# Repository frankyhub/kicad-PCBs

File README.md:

# KiCad-PCBs

Printed Circuit Boards - Vorlagen
- Download kicad: https://kicad-pcb.org/download/
- Docs kicad: https://docs.kicad-pcb.org/

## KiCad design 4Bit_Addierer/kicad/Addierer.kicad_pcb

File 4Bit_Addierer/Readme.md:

## 4-Bit Addierer Frontplatte und Platine

### Frontplatte

### Platine

### Schaltplan

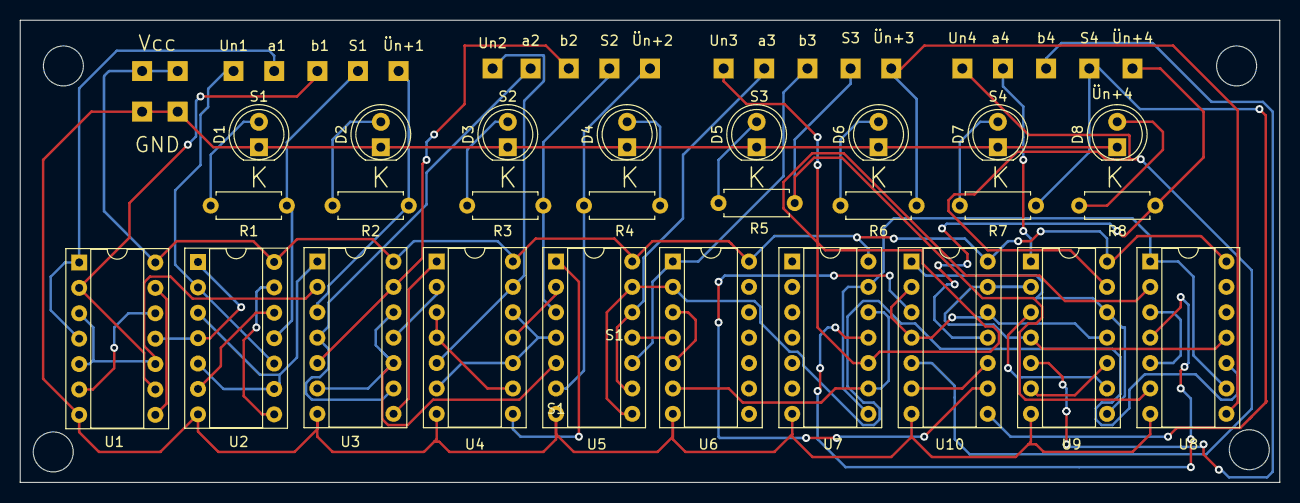
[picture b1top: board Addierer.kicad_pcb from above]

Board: 2 copper layers, 126.0 x 46.2 mm, 50 parts (0 on the bottom side), 58 nets.

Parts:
D1, D2, D3, D4, D5, D6, D7, D8: LED; LED_D5.0mm
GND1, GND1#3: LP_GND; LP
GND1#2: GND; LP
LP_Vcc1: LP_Vcc; LP
R1, R2, R3, R4, R5, R6, R7, R8: R; R_Axial_DIN0207_L6.3mm_D2.5mm_P7.62mm_Horizontal
S1: S1; LP
S2: S2; LP
S3: S3; LP
S4: S4; LP
U1, U2, U3, U4, U5, U6, U7, U8, U9, U10: 74LS00; DIP-14_W7.62mm_Socket
Un1: Un1; LP
Un2: Un2; LP
Un3: Un3; LP
Un4: Un4; LP
a1: a1; LP
a2: a2; LP
a3: a3; LP
a4: a4; LP
b1: b1; LP
b2: b2; LP
b3: b3; LP
b4: b4; LP
Ün+1: Ün+1; LP
Ün+2: Ün+2; LP
Ün+3: Ün+3; LP
Ün+4: Ün+4; LP

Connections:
+5V: GND1#2.1, LP_Vcc1.1, U1.14, U2.14, U3.14, U4.14, U5.14, U6.14, U7.14, U8.14, U9.14, U10.14
unnamed: D1.2, R1.2
unnamed: D2.2, R2.2
unnamed: D3.2, R3.2
unnamed: D4.2, R4.2
unnamed: D5.2, R5.2
unnamed: D6.2, R6.2
unnamed: D7.2, R7.2
unnamed: D8.2, R8.2
unnamed: D1.1, D2.1, D3.1, D4.1, D5.1, D6.1, D7.1, D8.1, GND1.1, GND1#3.1, U1.7, U2.7, U3.7, U4.7, U5.7, U6.7, U7.7, U8.7, U9.7, U10.7
unnamed: R1.1, S1.1, U2.11
unnamed: R2.1, U3.3, Ün+1.1
unnamed: R3.1, S2.1, U5.3
unnamed: R4.1, U5.6, Ün+2.1
unnamed: R5.1, S3.1, U8.6
unnamed: R6.1, U8.8, Ün+3.1
unnamed: R7.1, S4.1, U10.8
unnamed: R8.1, U10.11, Ün+4.1
unnamed: U1.1, U1.4, a1.1
unnamed: U1.2, U1.9, b1.1
unnamed: U1.3, U1.5, U1.10, U3.2
unnamed: U1.11, U2.1, U2.4
unnamed: U1.6, U1.12
unnamed: U1.8, U1.13
unnamed: U2.3, U2.5, U2.9, U3.1
unnamed: U2.2, U2.10, Un1.1
unnamed: U2.6, U2.12
unnamed: U2.8, U2.13
unnamed: U3.4, U3.9, a2.1
unnamed: U3.8, U4.1
unnamed: U3.6, U3.10, U3.12, U5.5
unnamed: U3.11, U4.2
unnamed: U3.5, U3.13, b2.1
unnamed: U4.3, U4.4, U4.9
unnamed: U4.8, U5.1
unnamed: U4.6, U4.10, U4.12, U5.4
unnamed: U4.11, U5.2
unnamed: U4.5, U4.13, Un2.1
unnamed: U5.10, U6.1, b3.1
unnamed: U5.11, U6.4
unnamed: U5.9, U5.12, a3.1
unnamed: U5.8, U5.13, U6.2, U8.10
unnamed: U6.3, U6.5
unnamed: U6.6, U7.9, U7.12
unnamed: U7.10, U8.2, Un3.1
unnamed: U7.11, U8.4
unnamed: U7.8, U7.13, U8.1, U8.9
unnamed: U8.3, U8.5
unnamed: U9.1, a4.1
unnamed: U9.3, U9.9
unnamed: U9.5, b4.1
unnamed: U9.6, U9.10
unnamed: U9.8, U9.12, U10.1
unnamed: U10.3, U10.9
unnamed: U9.13, U10.5, Un4.1
unnamed: U10.6, U10.10
unnamed: U9.11, U10.2, U10.4, U10.12
unnamed: U8.11, U9.2, U9.4, U10.13

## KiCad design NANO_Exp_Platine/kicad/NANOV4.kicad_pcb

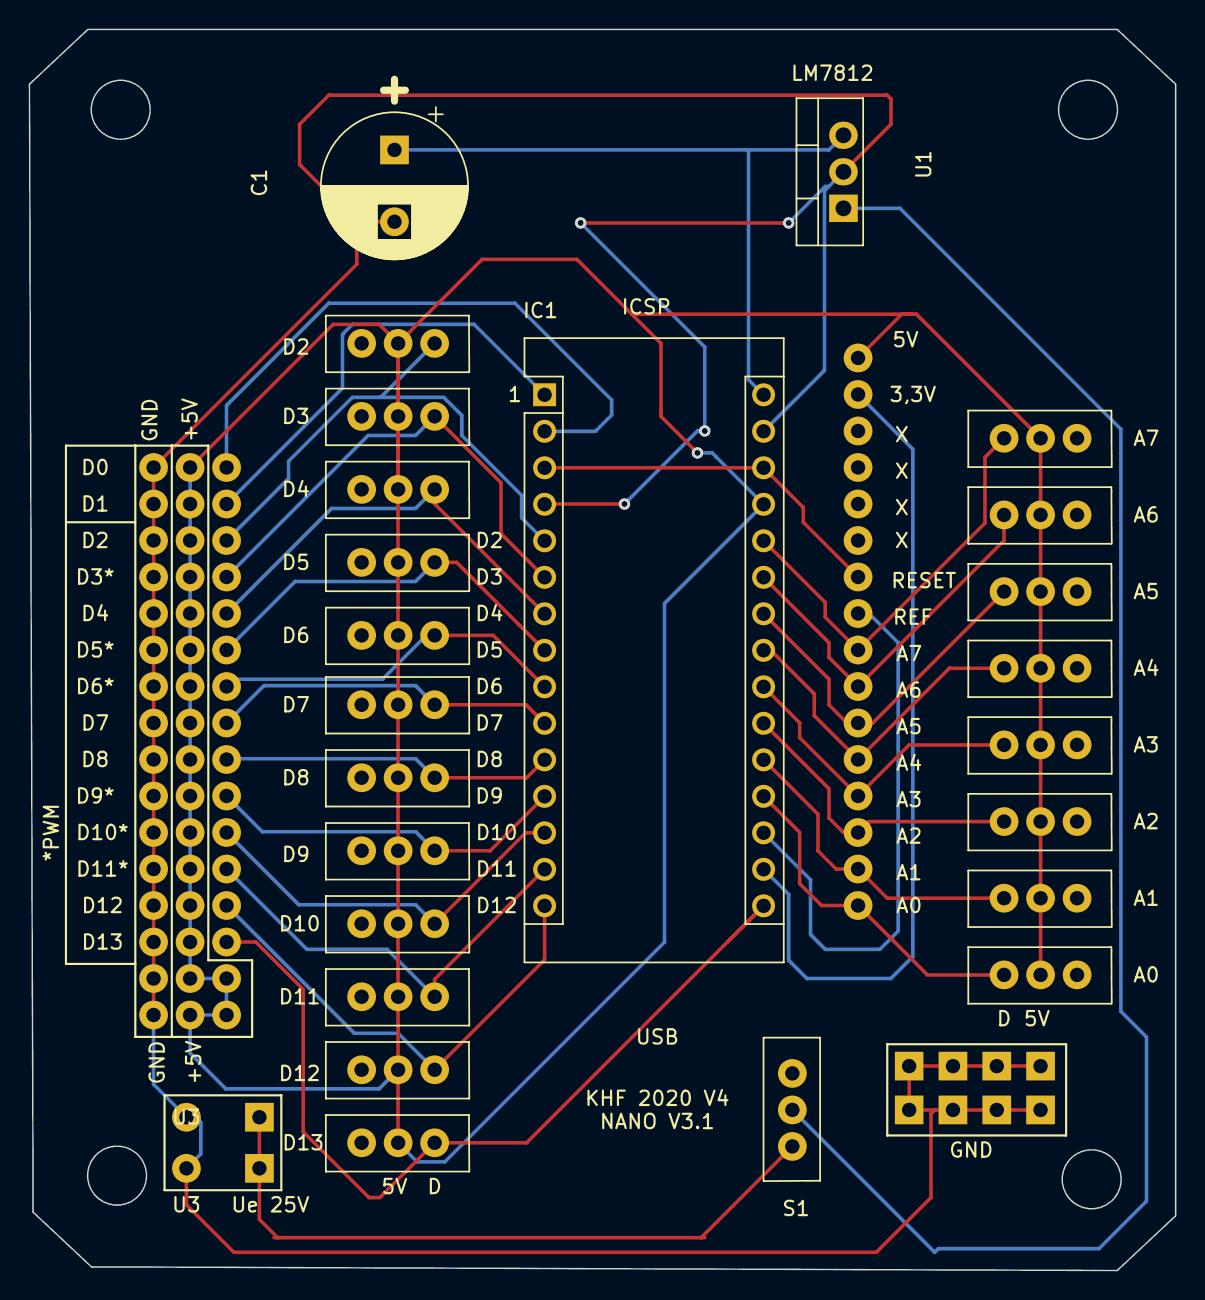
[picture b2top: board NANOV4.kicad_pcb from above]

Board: 2 copper layers, 79.8 x 86.4 mm, 38 parts (0 on the bottom side), 30 nets.

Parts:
A0, A1, A2, A3, A4, A5, A6, A7: Micro_Schalter; Micro_SchalterKHF
C1: CAP; CP_Radial_D10.0mm_P5.00mm
D2, D3, D4, D5, D6, D7, D8, D9, D10, D11, D12, D13: Micro_Schalter; Micro_SchalterKHF
IC1: Arduino_Nano_v3.x; Arduino_Nano
J1, J2, J3, J4: NANO16PINStiftleiste; NANO_Stift_16PIN
LP: LP
LP#2, LP#3, LP#4, LP#6, LP#7, LP#8: LP
LP#5: GND; LP
S1: Micro_Schalter; Micro_SchalterKHF
U1: LM7812_TO220; TO-220-3_Vertical
U3, U3#2: 9VBat; 9VBAT_khf

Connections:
+5V: A0.2, A1.2, A2.2, A3.2, A4.2, A5.2, A6.2, A7.2, D2.2, D3.2, D4.2, D5.2, D6.2, D7.2, D8.2, D9.2, D10.2, D11.2, D12.2, D13.2, IC1.27, J2.1, J2.2, J2.3, J2.4, J2.5, J2.6, J2.7, J2.8, J2.9, J2.10, J2.11, J2.12, J2.13, J2.14, J2.15, J2.16, J3.15, J3.16, J4.16
GND: C1.2, IC1.4, IC1.29, J1.1, J1.2, J1.3, J1.4, J1.5, J1.6, J1.7, J1.8, J1.9, J1.10, J1.11, J1.12, J1.13, J1.14, J1.15, J1.16, LP.1, LP#2.1, LP#3.1, LP#4.1, LP#5.1, LP#6.1, LP#7.1, LP#8.1, U1.2, U3.1, U3#2.1
unnamed: A0.3, IC1.19, J4.1
unnamed: A1.3, IC1.20, J4.2
unnamed: A2.3, IC1.21, J4.3
unnamed: A3.3, IC1.22, J4.4
unnamed: A4.3, IC1.23, J4.5
unnamed: A5.3, IC1.24, J4.6
unnamed: A6.3, IC1.25, J4.7
unnamed: A7.3, IC1.26, J4.8
unnamed: C1.1, IC1.30, U1.3
unnamed: D2.1, IC1.5, J3.3
unnamed: D3.1, IC1.6, J3.4
unnamed: D4.1, IC1.7, J3.5
unnamed: D5.1, IC1.8, J3.6
unnamed: D6.1, IC1.9, J3.7
unnamed: D7.1, IC1.10, J3.8
unnamed: D8.1, IC1.11, J3.9
unnamed: D9.1, IC1.12, J3.10
unnamed: D10.1, IC1.13, J3.11
unnamed: D11.1, IC1.14, J3.12
unnamed: D12.1, IC1.15, J3.13
unnamed: D13.1, IC1.16, J3.14
unnamed: IC1.1, J3.2
unnamed: IC1.2, J3.1
unnamed: IC1.17, J4.15
unnamed: IC1.18, J4.9
unnamed: IC1.3, IC1.28, J4.10
unnamed: S1.1, U3.2, U3#2.2
unnamed: S1.2, U1.1

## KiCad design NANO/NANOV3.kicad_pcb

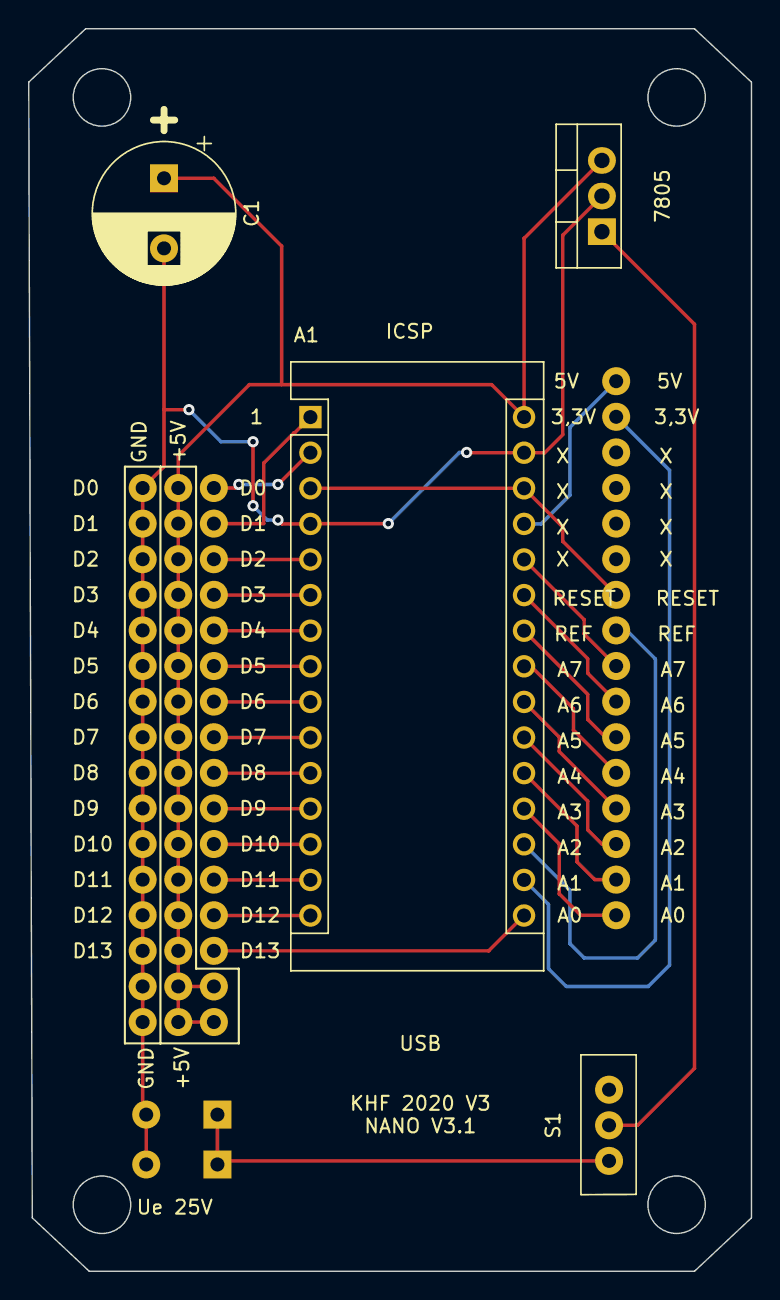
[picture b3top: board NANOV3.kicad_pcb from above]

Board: 2 copper layers, 51.6 x 88.6 mm, 10 parts (0 on the bottom side), 30 nets.

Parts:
7805: LM7805_TO220; TO-220-3_Vertical
A1: Arduino_Nano_v3.x; Arduino_Nano
C1: CAP; CP_Radial_D10.0mm_P5.00mm
J1, J2, J3, J4: NANO16PINStiftleiste; NANO_Stift_16PIN
S1: Micro_Schalter; Micro_SchalterKHF
U3, U3#2: 9VBat; 9VBAT_khf

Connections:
unnamed: A1.1, J3.2
unnamed: A1.2, J3.1
unnamed: A1.5, J3.3
unnamed: A1.6, J3.4
unnamed: A1.7, J3.5
unnamed: A1.8, J3.6
unnamed: A1.9, J3.7
unnamed: A1.10, J3.8
unnamed: A1.11, J3.9
unnamed: A1.12, J3.10
unnamed: A1.13, J3.11
unnamed: A1.14, J3.12
unnamed: A1.15, J3.13
unnamed: A1.16, J3.14
unnamed: A1.17, J4.15
unnamed: A1.18, J4.9
unnamed: A1.19, J4.1
unnamed: A1.20, J4.2
unnamed: A1.21, J4.3
unnamed: A1.22, J4.4
unnamed: A1.23, J4.5
unnamed: A1.24, J4.6
unnamed: A1.25, J4.7
unnamed: A1.26, J4.8
unnamed: A1.27, J4.16
unnamed: A1.3, A1.28, J4.10
unnamed: 7805.2, A1.4, A1.29, C1.2, J1.1, J1.2, J1.3, J1.4, J1.5, J1.6, J1.7, J1.8, J1.9, J1.10, J1.11, J1.12, J1.13, J1.14, J1.15, J1.16, U3.1, U3#2.1
unnamed: 7805.3, A1.30, C1.1, J2.1, J2.2, J2.3, J2.4, J2.5, J2.6, J2.7, J2.8, J2.9, J2.10, J2.11, J2.12, J2.13, J2.14, J2.15, J2.16, J3.15, J3.16
unnamed: S1.1, U3.2, U3#2.2
unnamed: 7805.1, S1.2

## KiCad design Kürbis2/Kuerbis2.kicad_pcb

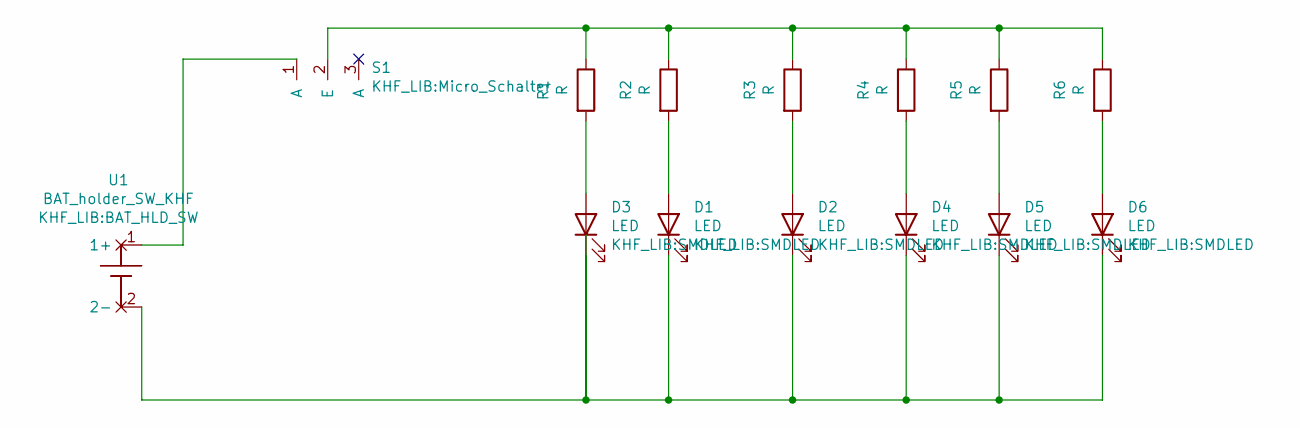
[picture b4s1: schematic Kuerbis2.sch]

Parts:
D1, D2, D3, D4, D5, D6: LED; SMDLED
R1, R2, R3, R4, R5, R6: R; R_Axial_DIN0309_L9.0mm_D3.2mm_P12.70mm_Horizontal
S1: Micro_Schalter
U1: BAT_holder_SW_KHF; BAT_HLD_SW

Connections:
unnamed: D1.1 (K), D2.1 (K), D3.1 (K), D4.1 (K), D5.1 (K), D6.1 (K), U1.2 (2-)
unnamed: D1.2 (A), R2.2
unnamed: D2.2 (A), R3.2
unnamed: D3.2 (A), R1.2
unnamed: D4.2 (A), R4.2
unnamed: D5.2 (A), R5.2
unnamed: D6.2 (A), R6.2
unnamed: R1.1, R2.1, R3.1, R4.1, R5.1, R6.1, S1.2 (E)
unnamed: S1.1 (A), U1.1 (1+)

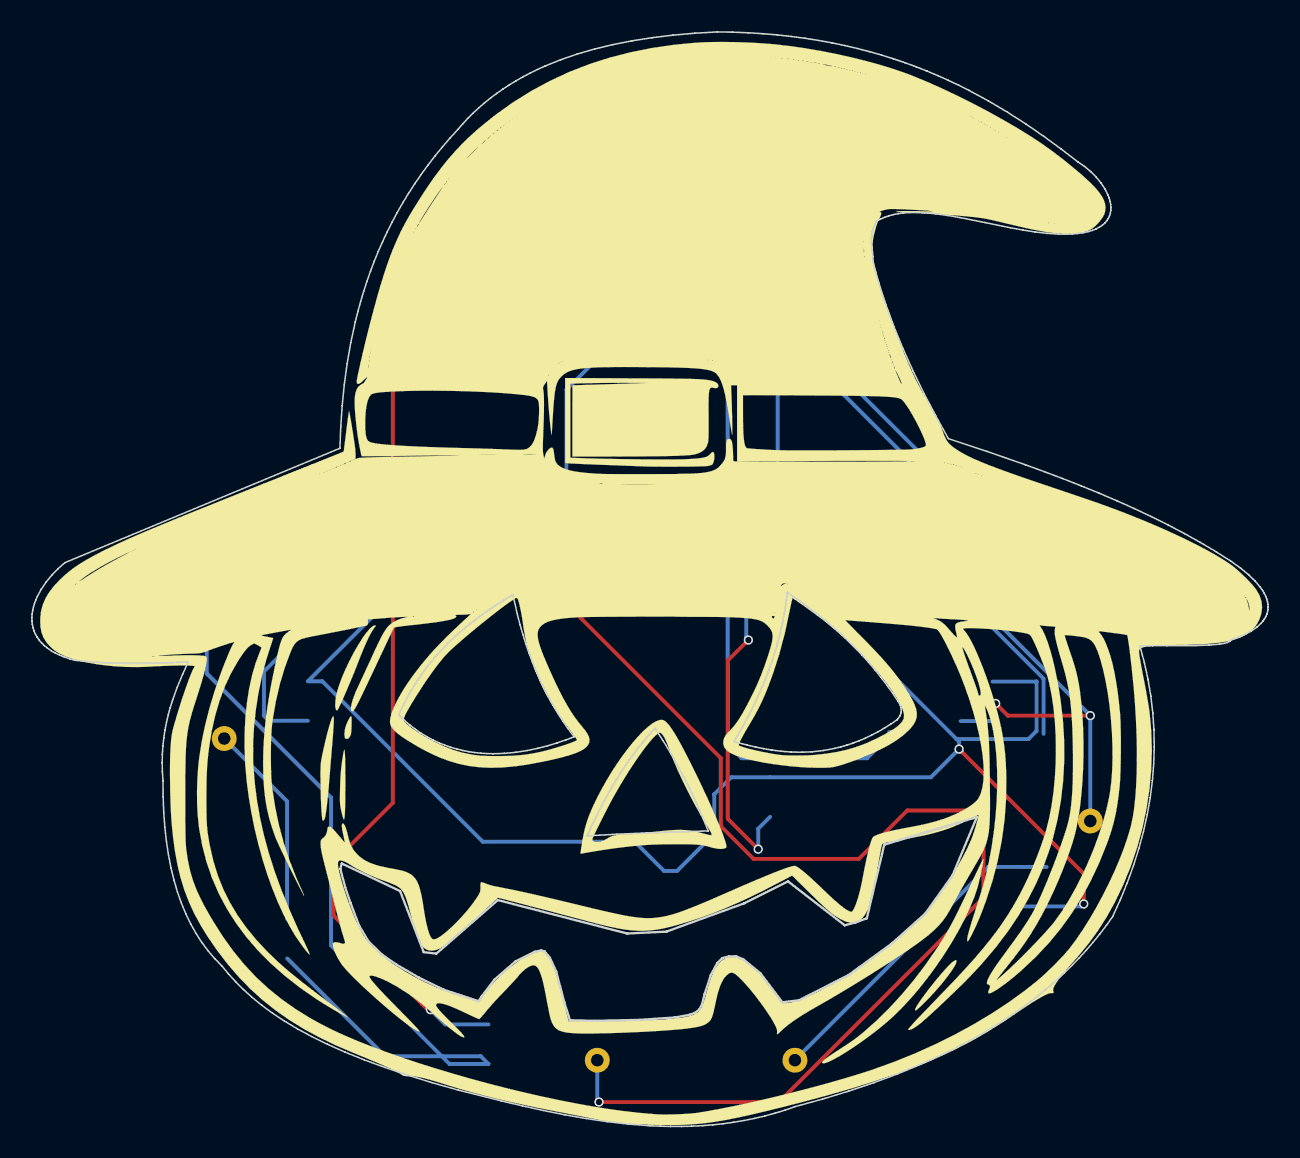
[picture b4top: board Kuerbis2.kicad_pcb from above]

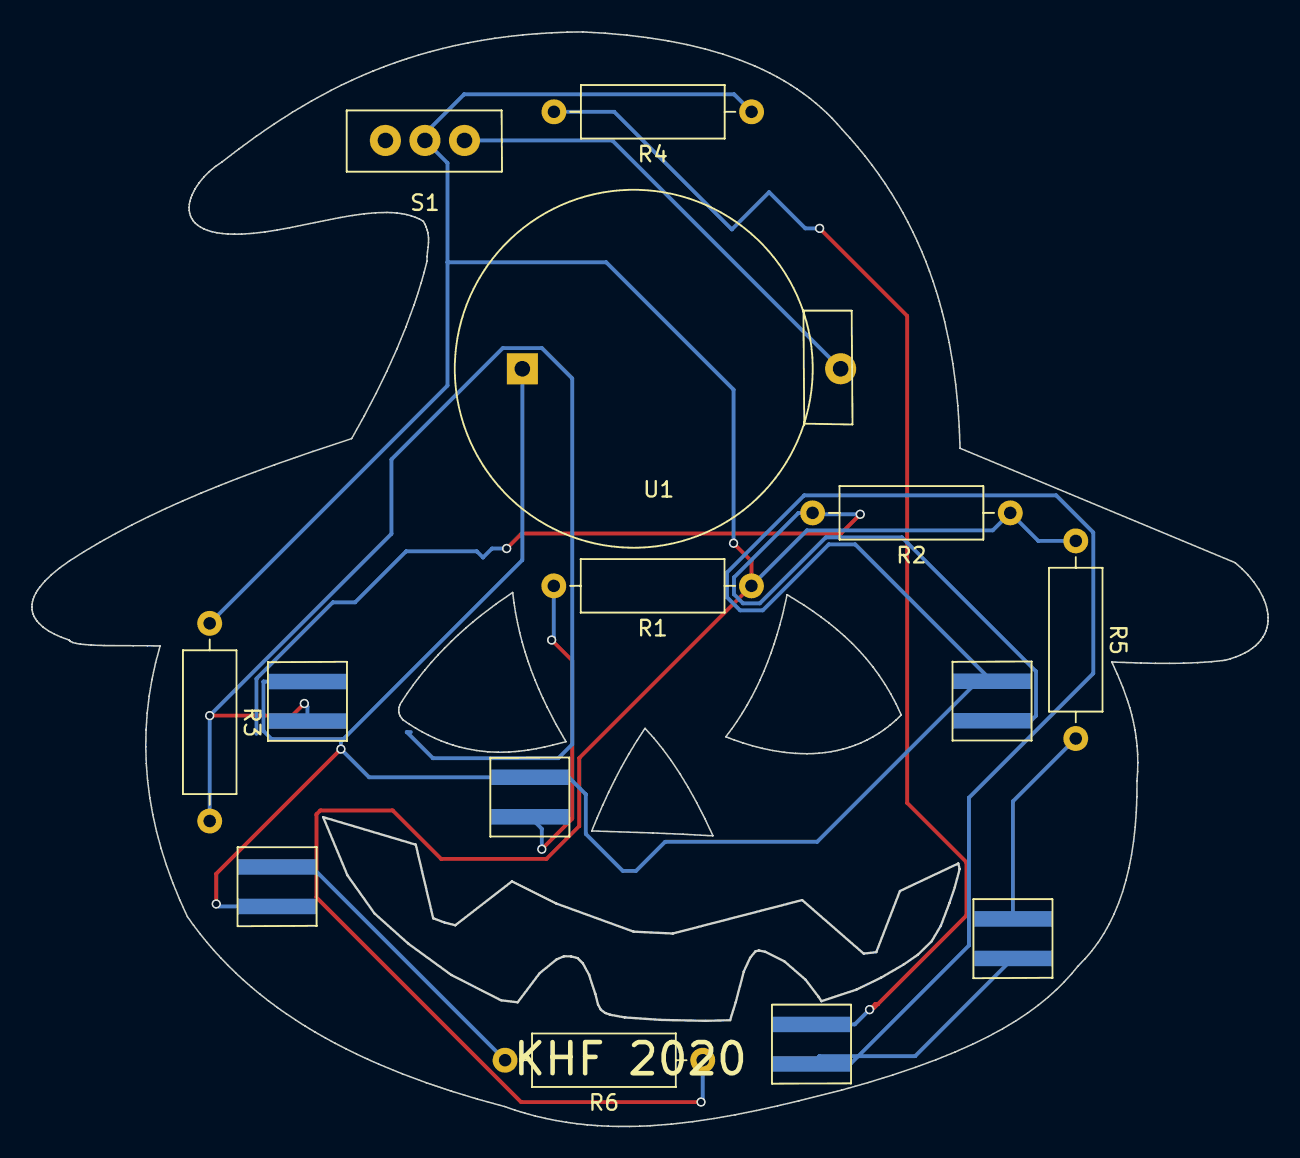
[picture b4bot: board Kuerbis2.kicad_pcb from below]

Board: 2 copper layers, 79.4 x 70.3 mm, 14 parts (14 on the bottom side), 9 nets.

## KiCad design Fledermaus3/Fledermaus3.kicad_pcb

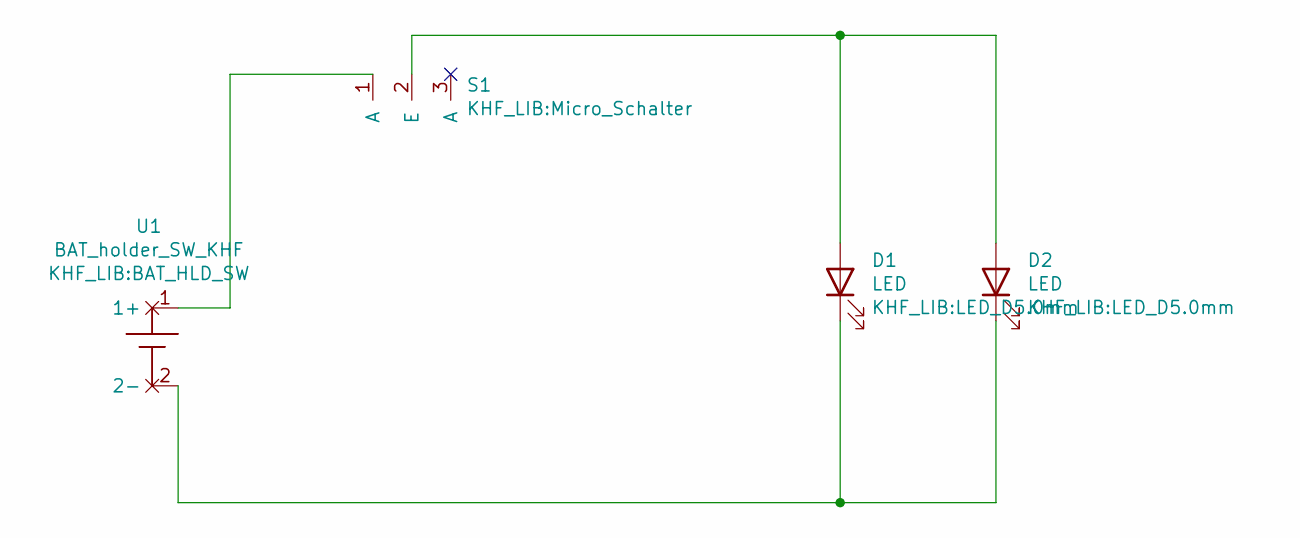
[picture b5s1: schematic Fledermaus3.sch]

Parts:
D1, D2: LED; LED_D5.0mm
S1: Micro_Schalter
U1: BAT_holder_SW_KHF; BAT_HLD_SW

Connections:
unnamed: D1.1 (K), D2.1 (K), U1.2 (2-)
unnamed: D1.2 (A), D2.2 (A), S1.2 (E)
unnamed: S1.1 (A), U1.1 (1+)

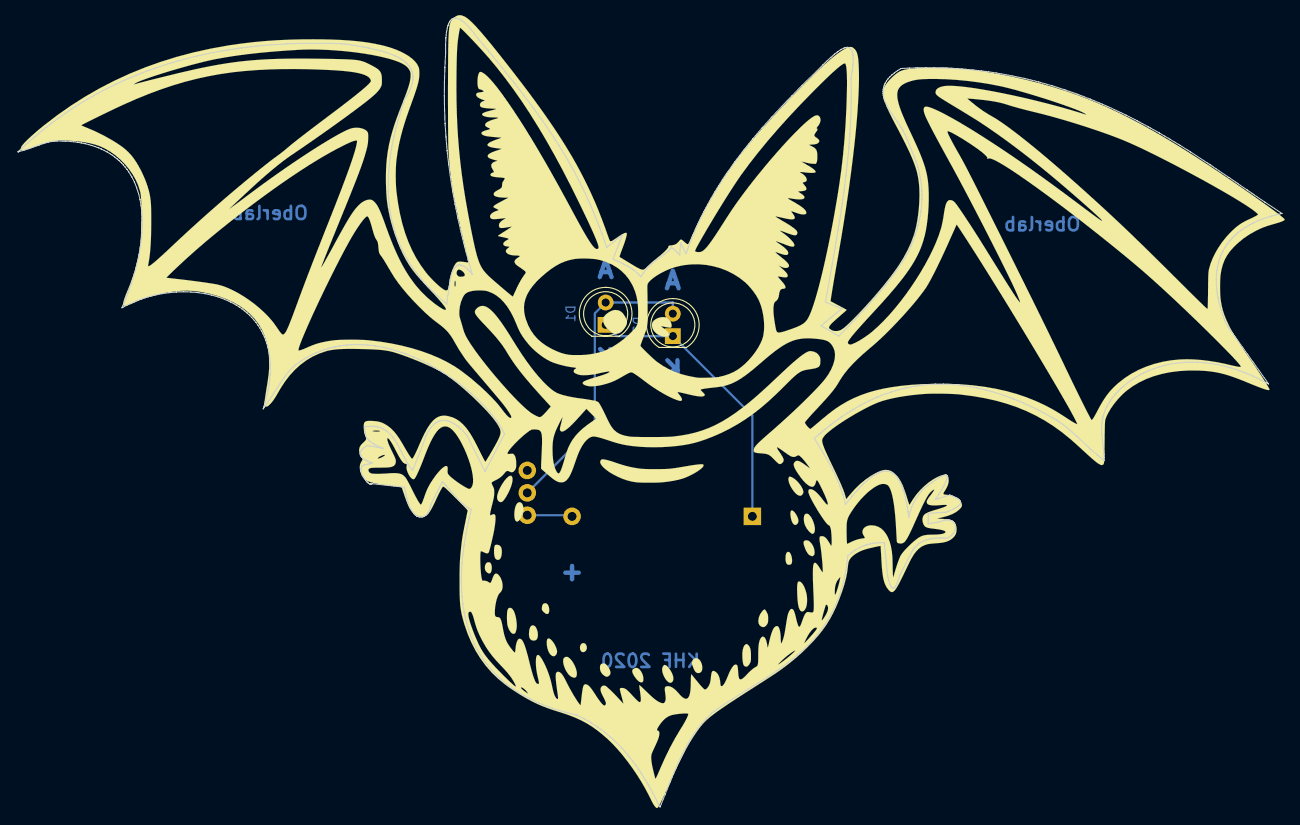
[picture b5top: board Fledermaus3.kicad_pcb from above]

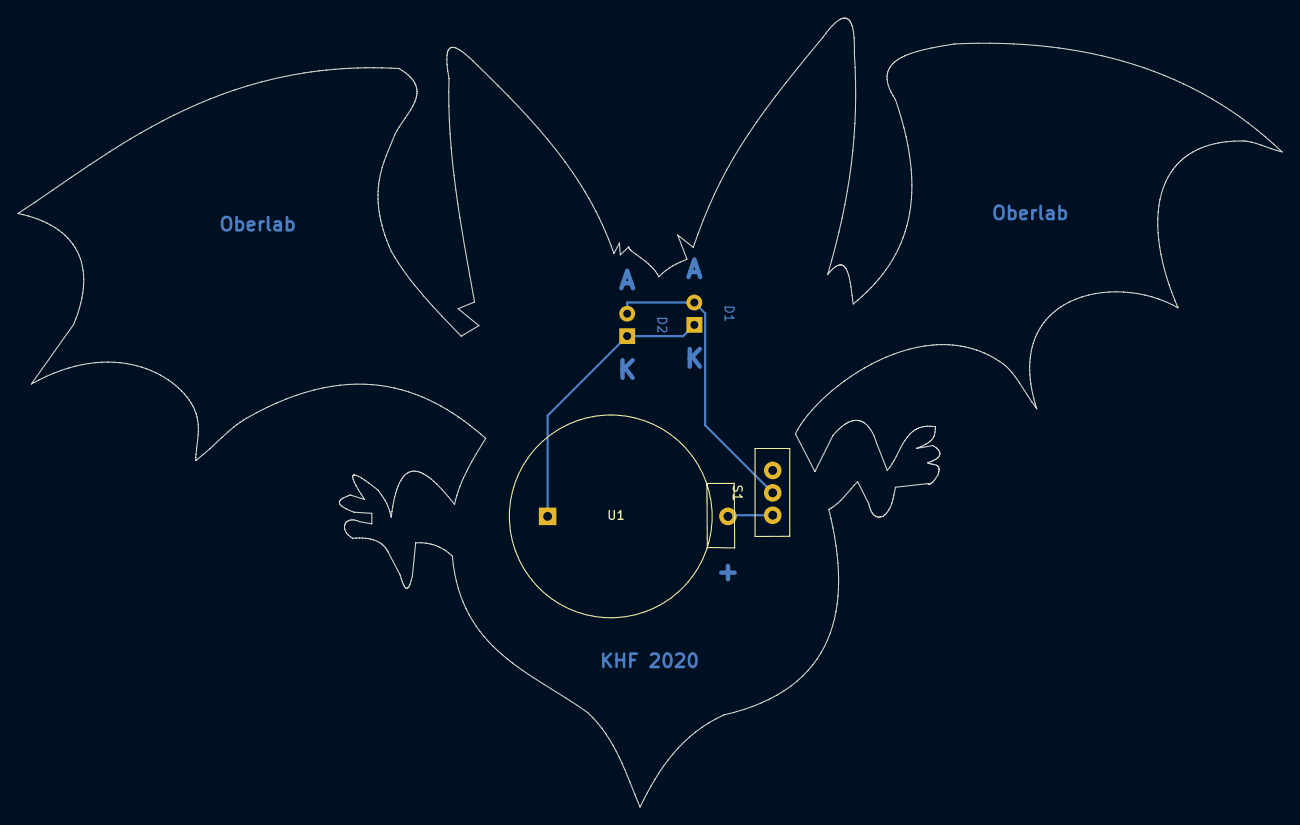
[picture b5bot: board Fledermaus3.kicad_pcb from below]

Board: 2 copper layers, 143.4 x 89.5 mm, 4 parts (2 on the bottom side), 3 nets.

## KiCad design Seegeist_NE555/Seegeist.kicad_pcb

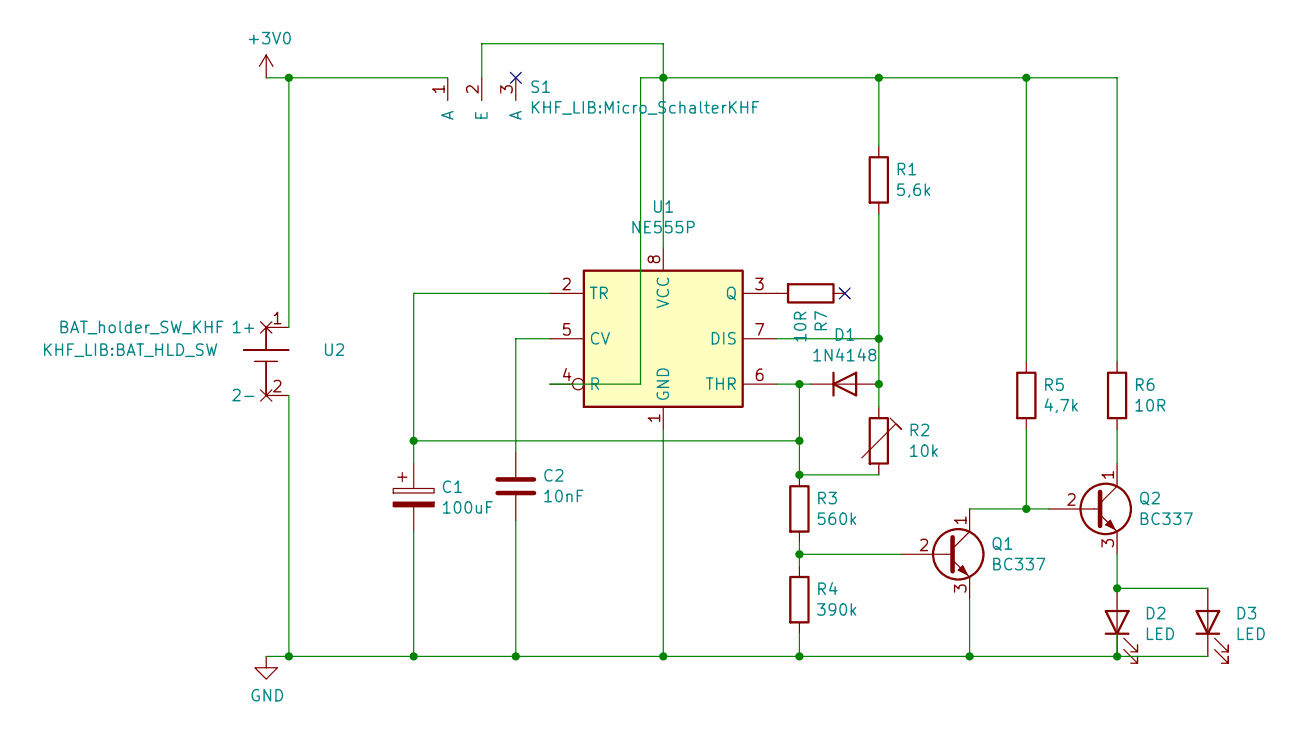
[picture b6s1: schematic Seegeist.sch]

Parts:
C1: 100uF; CP_Radial_D6.3mm_P2.50mm
C2: 10nF; C_Rect_L7.2mm_W3.5mm_P5.00mm_FKS2_FKP2_MKS2_MKP2
D1: 1N4148; D_DO-15_P3.81mm_Vertical_KathodeUp
D2, D3: LED; LED_D5.0mm
Q1, Q2: BC337; TO-92_Inline
R1: 5,6k; R_Axial_DIN0207_L6.3mm_D2.5mm_P10.16mm_Horizontal
R2: 10k; Potentiometer_Trimmer_Piher_PT-15h5_Vertical_Px5.0mm_Py10.0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
R3: 560k; R_Axial_DIN0207_L6.3mm_D2.5mm_P10.16mm_Horizontal
R4: 390k; R_Axial_DIN0207_L6.3mm_D2.5mm_P10.16mm_Horizontal
R5: 4,7k; R_Axial_DIN0207_L6.3mm_D2.5mm_P10.16mm_Horizontal
R6, R7: 10R; R_Axial_DIN0207_L6.3mm_D2.5mm_P10.16mm_Horizontal
S1: Micro_Schalter; Micro_SchalterKHF
U1: NE555P; DIP-8_W7.62mm
U2: BAT_holder_SW_KHF; BAT_HLD_SW

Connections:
+3V0: S1.1 (A), U2.1 (1+)
GND: C1.2, C2.2, D2.1 (K), D3.1 (K), Q1.3 (E), R4.2, U1.1 (GND), U2.2 (2-)
unnamed: C1.1, D1.1 (K), R2.2, R3.1, U1.2 (TR), U1.6 (THR)
unnamed: C2.1, U1.5 (CV)
unnamed: D1.2 (A), R1.2, R2.1, U1.7 (DIS)
unnamed: D2.2 (A), D3.2 (A), Q2.3 (E)
unnamed: Q1.1 (C), Q2.2 (B), R5.2
unnamed: Q1.2 (B), R3.2, R4.1
unnamed: Q2.1 (C), R6.2
unnamed: R1.1, R5.1, R6.1, S1.2 (E), U1.4 (R), U1.8 (VCC)
unnamed: R7.2, U1.3 (Q)

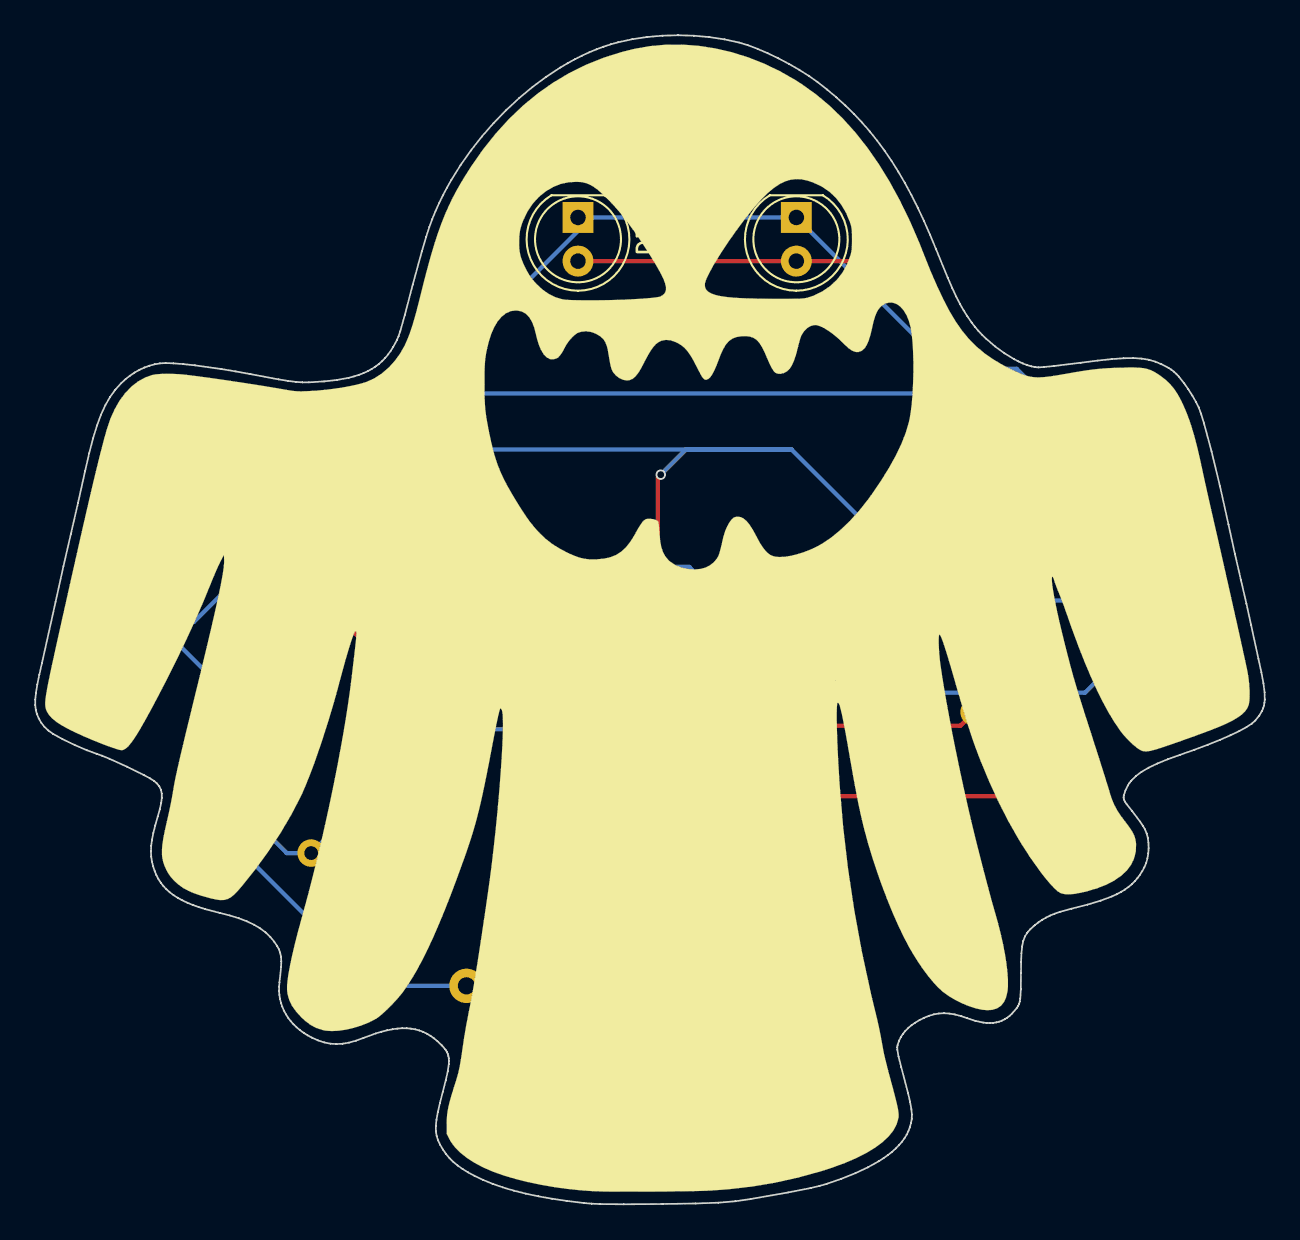
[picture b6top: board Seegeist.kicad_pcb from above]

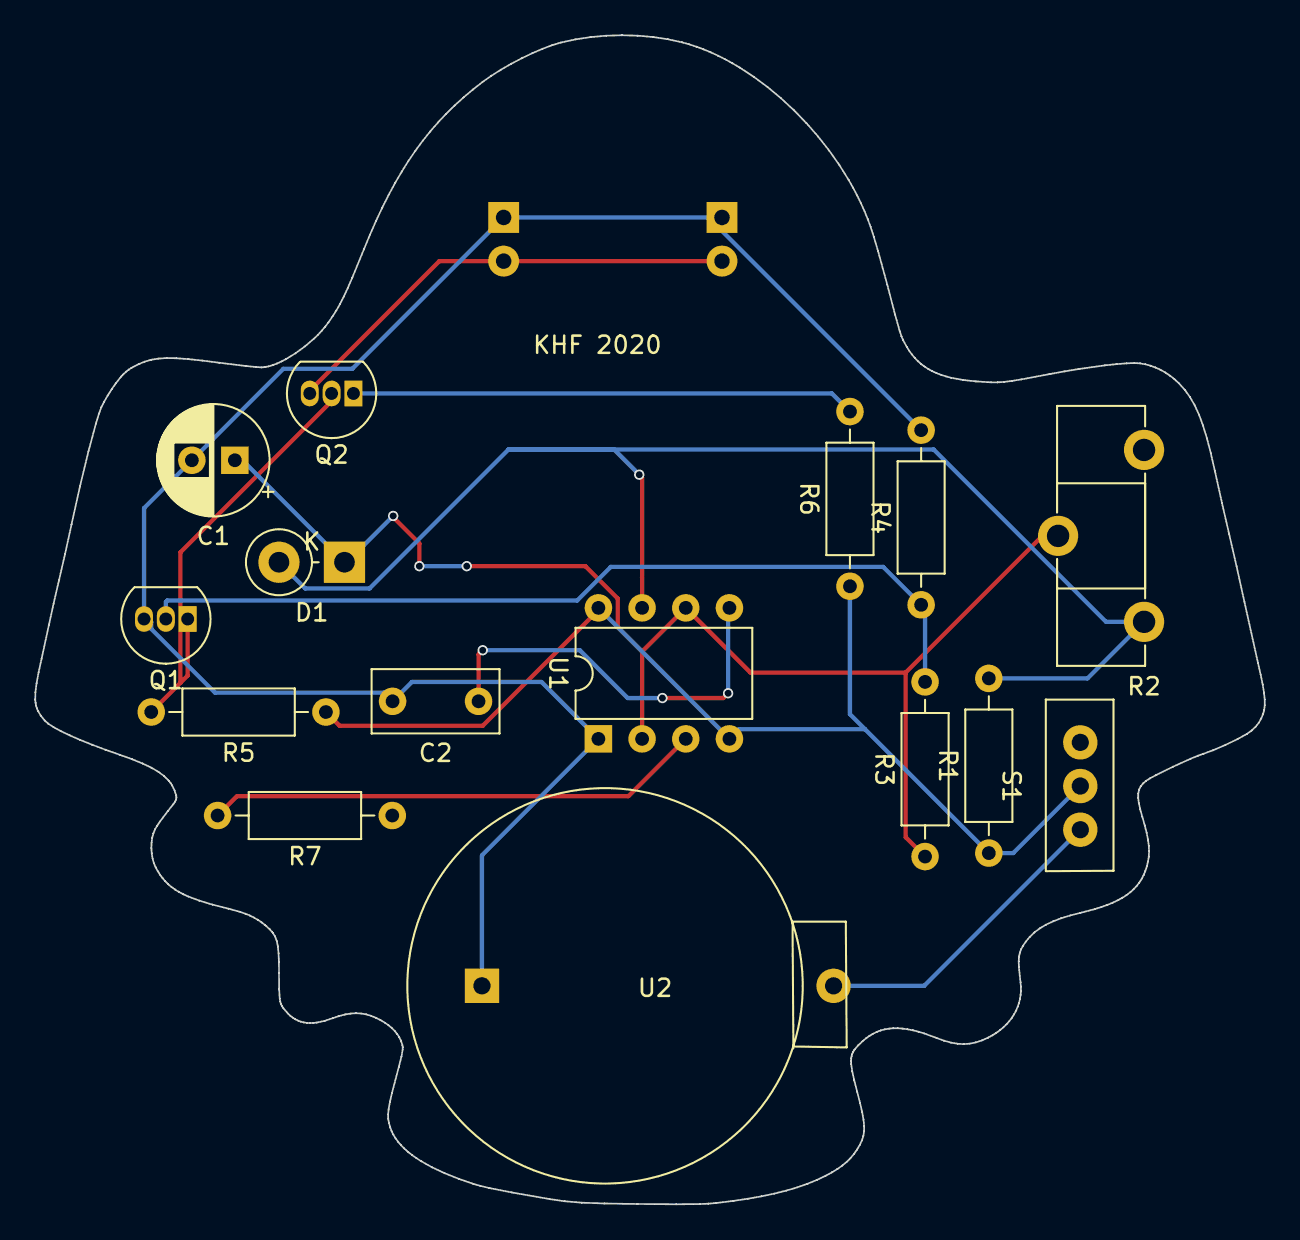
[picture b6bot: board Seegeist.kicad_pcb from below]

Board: 2 copper layers, 71.5 x 68.0 mm, 17 parts (15 on the bottom side), 11 nets.

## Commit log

2020-09-14 Create LICENSE
